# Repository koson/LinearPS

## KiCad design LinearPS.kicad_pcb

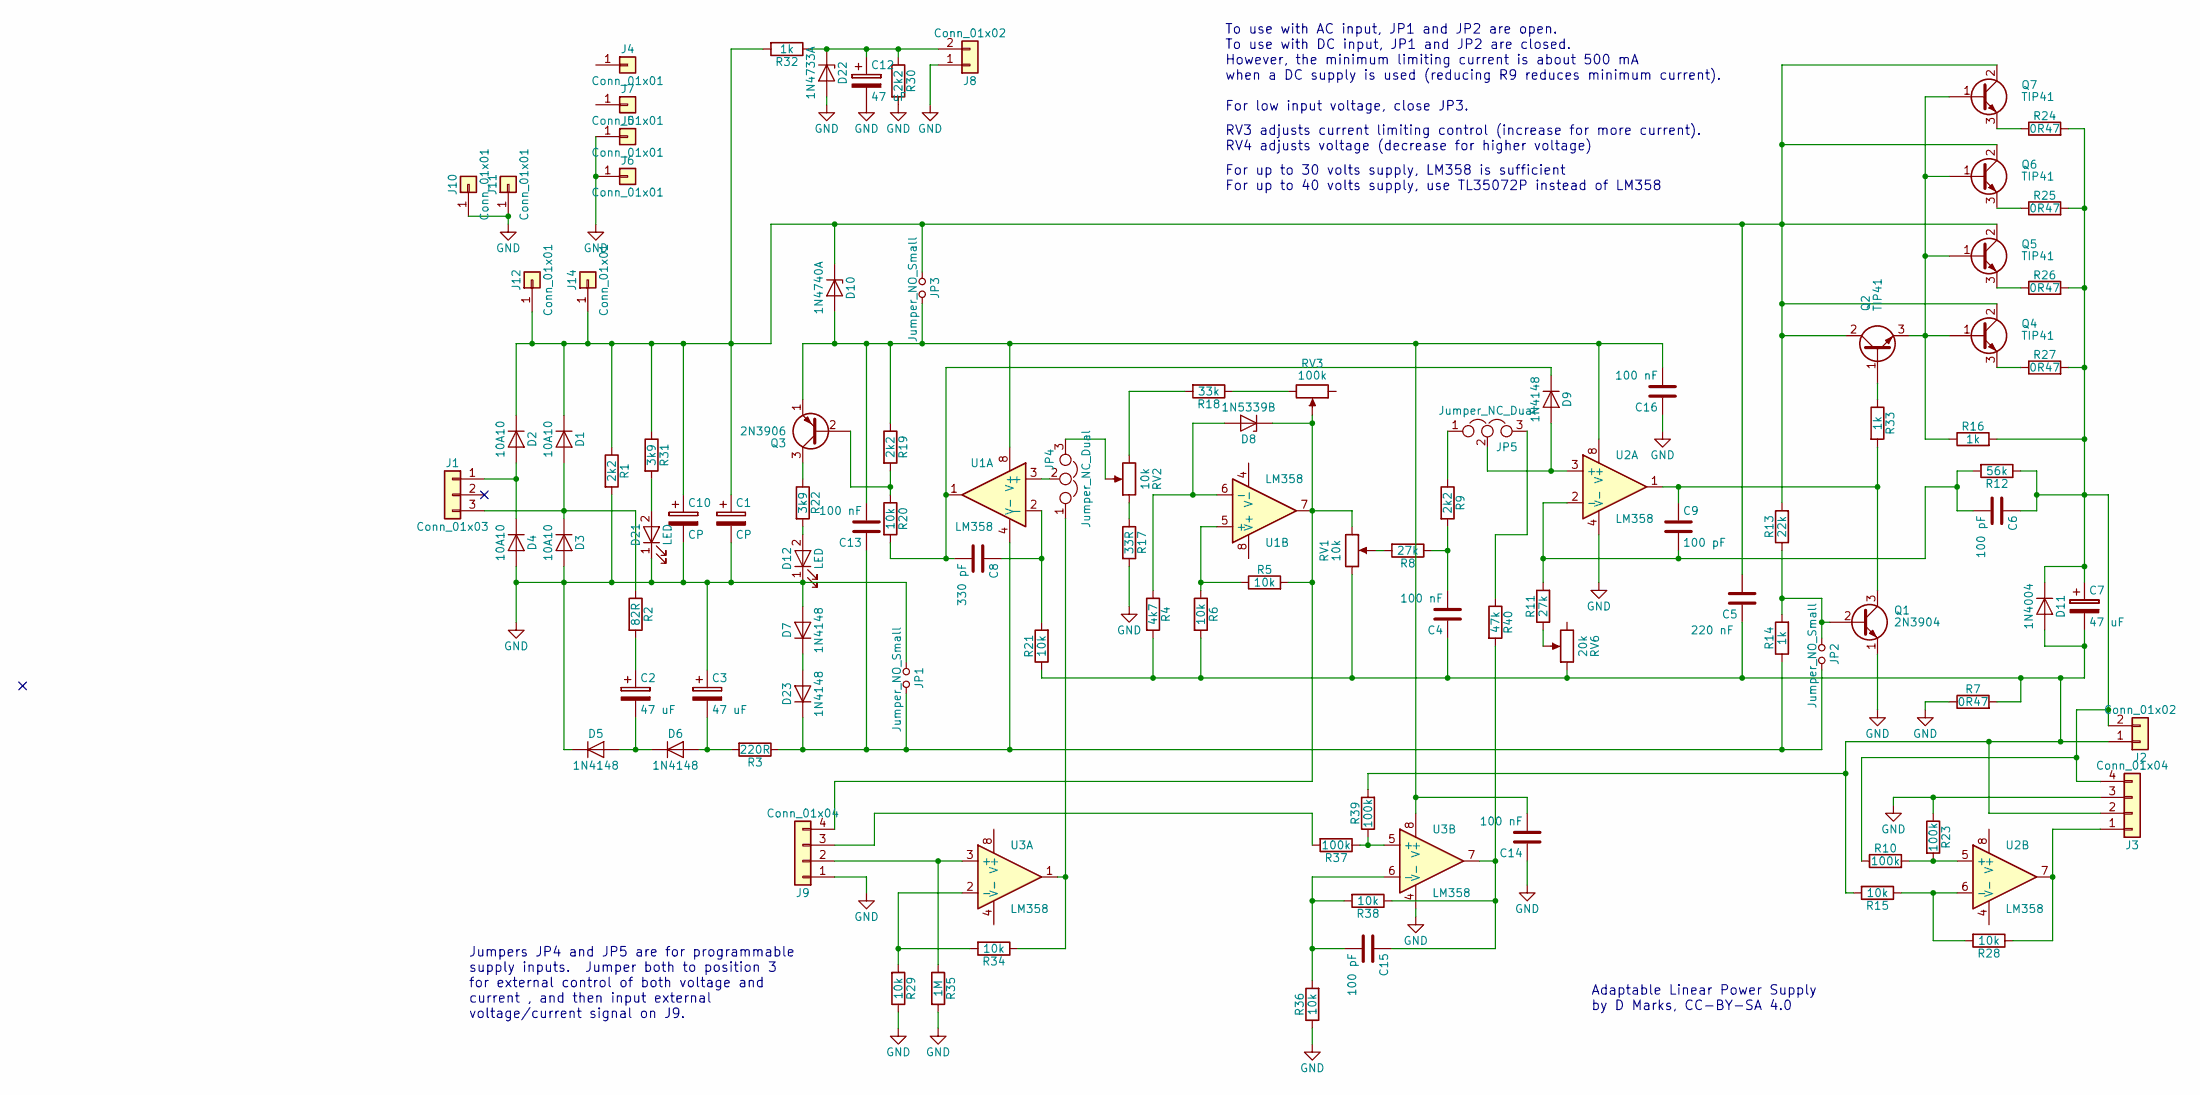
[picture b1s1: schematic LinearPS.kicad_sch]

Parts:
C1, C10: CP; CP_Radial_D18.0mm_P7.50mm
C2, C3, C7, C12: 47 uF; CP_Radial_D8.0mm_P5.00mm
C4, C13, C14, C16: 100 nF; C_Disc_D5.0mm_W2.5mm_P5.00mm
C5: 220 nF; C_Disc_D5.0mm_W2.5mm_P5.00mm
C6, C9, C15: 100 pF; C_Disc_D5.0mm_W2.5mm_P5.00mm
C8: 330 pF; C_Disc_D5.0mm_W2.5mm_P5.00mm
D1, D2, D3, D4: 10A10; D_P600_R-6_P12.70mm_Horizontal
D5, D6, D7, D9, D23: 1N4148; D_DO-35_SOD27_P7.62mm_Horizontal
D8: 1N5339B; D_DO-41_SOD81_P7.62mm_Horizontal
D10: 1N4740A; D_DO-41_SOD81_P7.62mm_Horizontal
D11: 1N4004; D_DO-41_SOD81_P7.62mm_Horizontal
D12, D21: LED; LED_D3.0mm
D22: 1N4733A; D_DO-41_SOD81_P7.62mm_Horizontal
J1: Conn_01x03; TerminalBlock_bornier-3_P5.08mm
J2: Conn_01x02; TerminalBlock_bornier-2_P5.08mm
J3, J9: Conn_01x04; Molex_KK-6410-04_04x2.54mm_Straight
J4, J5, J6, J7, J10, J11, J12, J14: Conn_01x01; 1pin
J8: Conn_01x02; Molex_KK-6410-02_02x2.54mm_Straight
JP1, JP2, JP3: Jumper_NO_Small; Pin_Header_Straight_1x02_Pitch2.54mm
JP4, JP5: Jumper_NC_Dual; Pin_Header_Straight_1x03_Pitch2.54mm
Q1: 2N3904; TO-92_Molded_Narrow
Q2: TIP41; TO-220-3_Vertical_WithPads
Q3: 2N3906; TO-92_Molded_Narrow
Q4, Q5, Q6, Q7: TIP41; TO-220-3_Vertical_WithBigPads
R1, R9, R19, R30: 2k2; R_Axial_DIN0207_L6.3mm_D2.5mm_P7.62mm_Horizontal
R2: 82R; R_Axial_DIN0411_L9.9mm_D3.6mm_P12.70mm_Horizontal
R3: 220R; R_Axial_DIN0411_L9.9mm_D3.6mm_P12.70mm_Horizontal
R4: 4k7; R_Axial_DIN0207_L6.3mm_D2.5mm_P7.62mm_Horizontal
R5, R6, R15, R20, R21, R28, R29, R34, R36, R38: 10k; R_Axial_DIN0207_L6.3mm_D2.5mm_P7.62mm_Horizontal
R7, R24, R25, R26, R27: 0R47; R_Axial_Power_L25.0mm_W6.4mm_P27.94mm
R8, R11: 27k; R_Axial_DIN0207_L6.3mm_D2.5mm_P7.62mm_Horizontal
R10, R23, R37, R39: 100k; R_Axial_DIN0207_L6.3mm_D2.5mm_P7.62mm_Horizontal
R12: 56k; R_Axial_DIN0207_L6.3mm_D2.5mm_P7.62mm_Horizontal
R13: 22k; R_Axial_DIN0207_L6.3mm_D2.5mm_P7.62mm_Horizontal
R14: 1k; R_Axial_DIN0207_L6.3mm_D2.5mm_P7.62mm_Horizontal
R16, R32, R33: 1k; R_Axial_DIN0411_L9.9mm_D3.6mm_P12.70mm_Horizontal
R17: 33R; R_Axial_DIN0207_L6.3mm_D2.5mm_P7.62mm_Horizontal
R18: 33k; R_Axial_DIN0207_L6.3mm_D2.5mm_P7.62mm_Horizontal
R22, R31: 3k9; R_Axial_DIN0207_L6.3mm_D2.5mm_P7.62mm_Horizontal
R35: 1M; R_Axial_DIN0207_L6.3mm_D2.5mm_P7.62mm_Horizontal
R40: 47k; R_Axial_DIN0207_L6.3mm_D2.5mm_P7.62mm_Horizontal
RV1, RV2: 10k; Potentiometer_WirePads
RV3: 100k; Potentiometer_Trimmer_Bourns_3296W
RV6: 20k; Potentiometer_Trimmer_Bourns_3296W
U1, U2, U3: LM358; DIP-8_W7.62mm_Socket

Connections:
GND: C1.2, C3.1, C10.2, C12.2, C14.1, C16.1, D3.2 (A), D4.2 (A), D5.1 (K), D7.2 (A), D12.1 (K), D21.1 (K), D22.2 (A), J3.3, J5.1, J6.1, J8.1, J9.1, J10.1, J11.1, JP1.1, Q1.1 (E), R1.2, R7.1, R17.2, R23.1, R29.1, R30.2, R35.2, R36.1, U2.4 (V-), U3.4 (V-)
unnamed: C1.1, C5.2, C10.1, D1.1 (K), D2.1 (K), D10.1 (K), J12.1, J14.1, JP3.1, Q2.2 (C), Q4.2 (C), Q5.2 (C), Q6.2 (C), Q7.2 (C), R1.1, R13.2, R31.1, R32.2
unnamed: C2.1, R2.2
unnamed: C2.2, D5.2 (A), D6.1 (K)
unnamed: C3.2, D6.2 (A), R3.2
unnamed: C4.1, C5.1, C7.2, D11.2 (A), J2.1, J3.2, R4.2, R6.2, R7.2, R15.2, R21.1, R39.2, RV1.3, RV6.1
unnamed: C4.2, R8.1, R9.2
unnamed: C6.1, C7.1, D11.1 (K), J2.2, J3.4, R10.1, R12.1, R16.2, R24.2, R25.2, R26.2, R27.2
unnamed: C6.2, C9.2, R11.2, R12.2, U2.2 (-)
unnamed: C8.1, R21.2, U1.2 (-)
unnamed: C8.2, D9.1 (K), R20.2, U1.1
unnamed: C9.1, Q1.3 (C), R33.2, U2.1
unnamed: C12.1, D22.1 (K), J8.2, R30.1, R32.1
unnamed: C13.1, D23.1 (K), JP1.2, JP2.2, R3.1, R14.1, U1.4 (V-)
unnamed: C13.2, C14.2, C16.2, D10.2 (A), JP3.2, Q3.1 (E), R19.1, U1.8 (V+), U2.8 (V+), U3.8 (V+)
unnamed: C15.1, R38.1, R40.2, U3.7
unnamed: C15.2, R36.2, R38.2, U3.6 (-)
unnamed: D1.2 (A), D3.1 (K), J1.3, R2.1
unnamed: D2.2 (A), D4.1 (K), J1.1
unnamed: D8.1 (K), J9.4, R5.2, RV1.1, RV3.2, U1.7
unnamed: D8.2 (A), R4.1, U1.6 (-)
unnamed: D9.2 (A), JP5.2, U2.3 (+)
unnamed: D12.2 (A), R22.2
unnamed: D21.2 (A), R31.2
unnamed: D7.1 (K), D23.2 (A)
unnamed: J3.1, R28.1, U2.7
unnamed: J9.2, R35.1, U3.3 (+)
unnamed: J9.3, R37.2
unnamed: JP2.1, Q1.2 (B), R13.1, R14.2
unnamed: JP4.1, R34.1, U3.1
unnamed: JP4.2, U1.3 (+)
unnamed: JP4.3, RV2.2
unnamed: JP5.1, R9.1
unnamed: JP5.3, R40.1
unnamed: Q2.1 (B), R33.1
unnamed: Q2.3 (E), Q4.1 (B), Q5.1 (B), Q6.1 (B), Q7.1 (B), R16.1
unnamed: Q3.2 (B), R19.2, R20.1
unnamed: Q3.3 (C), R22.1
unnamed: Q4.3 (E), R27.1
unnamed: Q5.3 (E), R26.1
unnamed: Q6.3 (E), R25.1
unnamed: Q7.3 (E), R24.1
unnamed: R5.1, R6.1, U1.5 (+)
unnamed: R8.2, RV1.2
unnamed: R10.2, R23.2, U2.5 (+)
unnamed: R11.1, RV6.2
unnamed: R15.1, R28.2, U2.6 (-)
unnamed: R17.1, RV2.1
unnamed: R18.1, RV3.3
unnamed: R18.2, RV2.3
unnamed: R29.2, R34.2, U3.2 (-)
unnamed: R37.1, R39.1, U3.5 (+)

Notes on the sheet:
Jumpers JP4 and JP5 are for programmable supply inputs. Jumper both to position 3 for external control of both voltage and current , and then input external voltage/current signal on J9.
To use with AC input, JP1 and JP2 are open. To use with DC input, JP1 and JP2 are closed. However, the minimum limiting current is about 500 mA when a DC supply is used (reducing R9 reduces minimum current). For low input voltage, close JP3.
RV3 adjusts current limiting control (increase for more current). RV4 adjusts voltage (decrease for higher voltage)
For up to 30 volts supply, LM358 is sufficient For up to 40 volts supply, use TL35072P instead of LM358
Adaptable Linear Power Supply by D Marks, CC-BY-SA 4.0

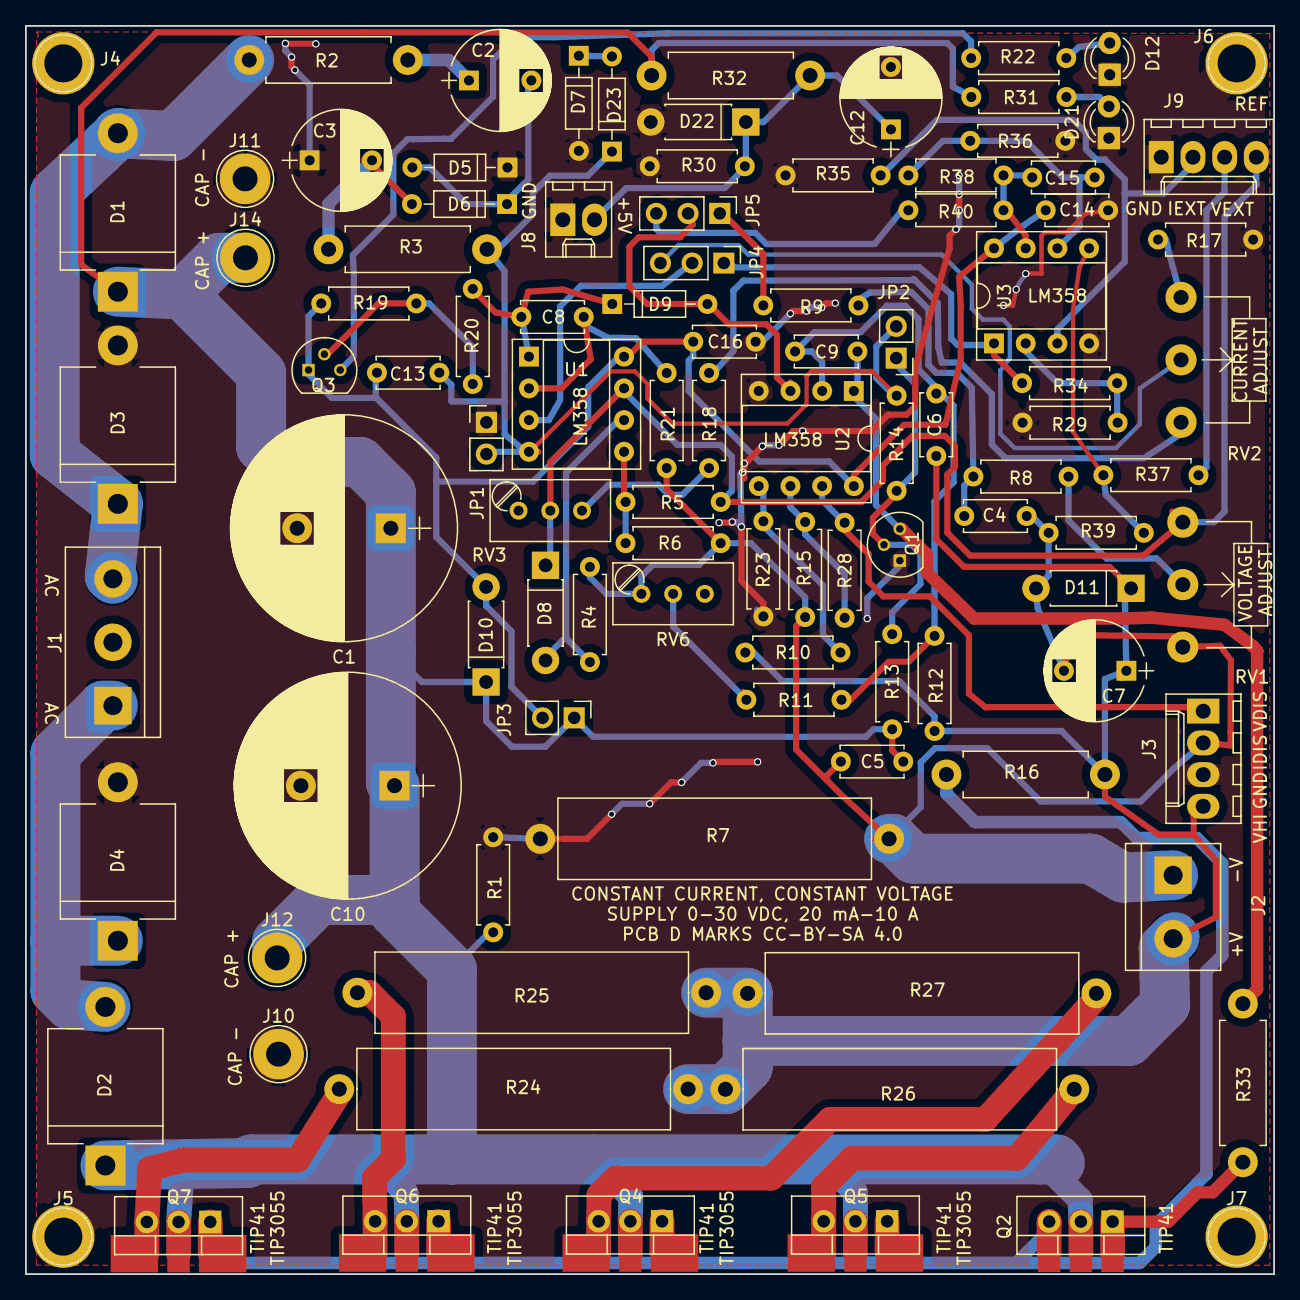
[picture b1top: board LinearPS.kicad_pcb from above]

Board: 2 copper layers, 100.0 x 100.0 mm, 102 parts (0 on the bottom side), 52 nets.

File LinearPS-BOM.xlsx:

Source: | F:\OneDrive\__PCB Works\LinearPS\LinearPS.kicad_sch
Date: | 44359.901342592595
Tool: | Eeschema (5.99.0-10447-gf083f043cb)
Generator: | C:\Program Files\KiCad\5.99\bin\scripting\plugins/bom_csv_grouped_by_value.py
Component Count: | 102
Item | Qty | Reference(s) | Value | LibPart | Footprint | Datasheet | Description | Part_Number
1 | 2 | C1, C10 | CP | LinearPS-rescue:CP | Capacitors_THT:CP_Radial_D18.0mm_P7.50mm | http://www.es.co.th/detail.asp?Prod=056603488 | E-Cap KM Series 4700uF/50Vdc -40 C to +105 C, 20% ,2000hrs. Miniature Sized | EKM478M1HL40RRSAP
2 | 4 | C2, C3, C7, C12 | 47 uF | LinearPS-rescue:CP | Capacitors_THT:CP_Radial_D8.0mm_P5.00mm | http://www.es.co.th/detail.asp?Prod=056601120 | E-Cap GS Series 4.7uF/400Volt | EGS475M2GF12RRSAP
3 | 4 | C4, C13, C14, C16 | 100 nF | LinearPS-rescue:C | Capacitors_THT:C_Disc_D5.0mm_W2.5mm_P5.00mm | http://www.es.co.th/detail.asp?Prod=015800183 | Ceramic Disc Cap 0.1uF/50V, -20/+80% Dia 7.5mm | S104ZYFE072L
4 | 1 | C5 | 220 nF | LinearPS-rescue:C | Capacitors_THT:C_Disc_D5.0mm_W2.5mm_P5.00mm | http://www.es.co.th/detail.asp?Prod=015802865 | Ceramic Disc Cap 0.22uF/50Vdc, -20/+80%,Y5V | S224ZYFE082LF
5 | 3 | C6, C9, C15 | 100 pF | LinearPS-rescue:C | Capacitors_THT:C_Disc_D5.0mm_W2.5mm_P5.00mm | http://www.es.co.th/detail.asp?Prod=015800245 | Ceramic Disc Cap 100pF/50Vdc, 10% | T101KCHE062L
6 | 1 | C8 | 330 pF | LinearPS-rescue:C | Capacitors_THT:C_Disc_D5.0mm_W2.5mm_P5.00mm | http://www.es.co.th/detail.asp?Prod=015802125 | Ceramic Disc Cap 330pF/50Vdc, 10% | H331KYAE052A-T
7 | 4 | D1, D2, D3, D4 | 10A10 | LinearPS-rescue:D | Diodes_THT:D_P600_R-6_P12.70mm_Horizontal
8 | 5 | D5, D6, D7, D9, D23 | 1N4148 | LinearPS-rescue:D | Diodes_THT:D_DO-35_SOD27_P7.62mm_Horizontal | http://www.es.co.th/detail.asp?Prod=029901371 | Fast Switching Diodes 100V/200mA trr 4ns | PH1N4148TB
9 | 1 | D8 | 1N5339B | LinearPS-rescue:D_Zener | Diodes_THT:D_DO-41_SOD81_P7.62mm_Horizontal | http://www.es.co.th/detail.asp?Prod=013500933 | ZENER DIODE 5.6V/1.3W, Iz=45mA | 1N4734A-TAP
10 | 1 | D10 | 1N4740A | LinearPS-rescue:D_Zener | Diodes_THT:D_DO-41_SOD81_P7.62mm_Horizontal | http://www.es.co.th/detail.asp?Prod=029900847 | Zener Diodes 1W/10V , Iz= 25mA Hermetically Sealed Glass Zener Voltage Regulator | 1N4740ATA-TC/ON
11 | 1 | D11 | 1N4004 | LinearPS-rescue:D | Diodes_THT:D_DO-41_SOD81_P7.62mm_Horizontal | http://www.es.co.th/detail.asp?Prod=030800029 | Silicon Rectifiers Diode 400V/1A | 1N4004-JJ
12 | 2 | D12, D21 | LED | LinearPS-rescue:LED | LEDs:LED_D3.0mm | http://www.es.co.th/detail.asp?Prod=001000491 | LED Round 3mm,4mcd,Red Color Red Diffused Lens | TOL-30BHRADAA
13 | 1 | D22 | 1N4733A | LinearPS-rescue:D_Zener | Diodes_THT:D_DO-41_SOD81_P7.62mm_Horizontal | http://www.es.co.th/detail.asp?prod=029900727 | Zener Diodes 1W/5.1V, Iz = 49mA Hermetically Sealed Glass Zener Voltage Regulat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 | 1N4733ATA-TC/ON
14 | 1 | J1 | Conn_01x03 | LinearPS-rescue:Conn_01x03 | Connectors_Terminal_Blocks:TerminalBlock_bornier-3_P5.08mm
15 | 1 | J2 | Conn_01x02 | LinearPS-rescue:Conn_01x02 | Connectors_Terminal_Blocks:TerminalBlock_bornier-2_P5.08mm
16 | 2 | J3, J9 | Conn_01x04 | LinearPS-rescue:Conn_01x04 | Connectors_Molex:Molex_KK-6410-04_04x2.54mm_Straight
17 | 8 | J4, J5, J6, J7, J10, J11, J12, J14 | Conn_01x01 | LinearPS-rescue:Conn_01x01 | Connectors:1pin
18 | 1 | J8 | Conn_01x02 | LinearPS-rescue:Conn_01x02 | Connectors_Molex:Molex_KK-6410-02_02x2.54mm_Straight
19 | 3 | JP1, JP2, JP3 | Jumper_NO_Small | LinearPS-rescue:Jumper_NO_Small | Pin_Headers:Pin_Header_Straight_1x02_Pitch2.54mm
20 | 2 | JP4, JP5 | Jumper_NC_Dual | LinearPS-rescue:Jumper_NC_Dual | Pin_Headers:Pin_Header_Straight_1x03_Pitch2.54mm
21 | 1 | Q1 | 2N3904 | LinearPS-rescue:2N3904 | TO_SOT_Packages_THT:TO-92_Molded_Narrow | http://www.es.co.th/detail.asp?prod=012302944 | Transistor NPN 40V/0.2A,for General Purpose Amplifier and Switch, Useful Dynami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 | 2N3904TA
22 | 1 | Q2 | TIP41 | LinearPS-rescue:TIP41 | linearps:TO-220-3_Vertical_WithPads | http://www.es.co.th/detail.asp?prod=008304245 | Silicon Power Transistors NPN 100V/6A Medium Power Linear and Switching Applica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 | TIP41C
23 | 1 | Q3 | 2N3906 | LinearPS-rescue:2N3906 | TO_SOT_Packages_THT:TO-92_Molded_Narrow | http://www.es.co.th/detail.asp?Prod=012302600 | Transistor PNP 40V/0.2A for General Purpose Amplifier and Switching Application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 | 2N3906TA
24 | 4 | Q4, Q5, Q6, Q7 | TIP41 | LinearPS-rescue:TIP41 | linearps:TO-220-3_Vertical_WithBigPads | http://www.es.co.th/detail.asp?prod=008304245 | Silicon Power Transistors NPN 100V/6A Medium Power Linear and Switching Applica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 | TIP41C
25 | 4 | R1, R9, R19, R30 | 2k2 | LinearPS-rescue:R | Resistors_THT:R_Axial_DIN0207_L6.3mm_D2.5mm_P7.62mm_Horizontal |  |  | R 2k2 1/4W 5%
26 | 1 | R2 | 82R | LinearPS-rescue:R | Resistors_THT:R_Axial_DIN0411_L9.9mm_D3.6mm_P12.70mm_Horizontal |  |  | R 82E 1W 5%
27 | 1 | R3 | 220R | LinearPS-rescue:R | Resistors_THT:R_Axial_DIN0411_L9.9mm_D3.6mm_P12.70mm_Horizontal |  |  | R 220E 1W 5%
28 | 1 | R4 | 4k7 | LinearPS-rescue:R | Resistors_THT:R_Axial_DIN0207_L6.3mm_D2.5mm_P7.62mm_Horizontal |  |  | R 4k7 1/4W 5%
29 | 10 | R5, R6, R15, R20, R21, R28, R29, R34, R36, R38 | 10k | LinearPS-rescue:R | Resistors_THT:R_Axial_DIN0207_L6.3mm_D2.5mm_P7.62mm_Horizontal |  |  | R 10k 1/4W 5%
30 | 5 | R7, R24, R25, R26, R27 | 0R47 | LinearPS-rescue:R | Resistors_THT:R_Axial_Power_L25.0mm_W6.4mm_P27.94mm |  |  | R 0R47 5W 5%
31 | 2 | R8, R11 | 27k | LinearPS-rescue:R | Resistors_THT:R_Axial_DIN0207_L6.3mm_D2.5mm_P7.62mm_Horizontal |  |  | R 27k 1/4W 5%
32 | 4 | R10, R23, R37, R39 | 100k | LinearPS-rescue:R | Resistors_THT:R_Axial_DIN0207_L6.3mm_D2.5mm_P7.62mm_Horizontal |  |  | R 100k 1/4W 5%
33 | 1 | R12 | 56k | LinearPS-rescue:R | Resistors_THT:R_Axial_DIN0207_L6.3mm_D2.5mm_P7.62mm_Horizontal |  |  | R 56k 1/4W 5%
34 | 1 | R13 | 22k | LinearPS-rescue:R | Resistors_THT:R_Axial_DIN0207_L6.3mm_D2.5mm_P7.62mm_Horizontal |  |  | R 22k 1/4W 5%
35 | 1 | R14 | 1k | LinearPS-rescue:R | Resistors_THT:R_Axial_DIN0207_L6.3mm_D2.5mm_P7.62mm_Horizontal |  |  | R 1k 1/4W 5%
36 | 3 | R16, R32, R33 | 1k | LinearPS-rescue:R | Resistors_THT:R_Axial_DIN0411_L9.9mm_D3.6mm_P12.70mm_Horizontal |  |  | R 1k 1W 5%
37 | 1 | R17 | 33R | LinearPS-rescue:R | Resistors_THT:R_Axial_DIN0207_L6.3mm_D2.5mm_P7.62mm_Horizontal |  |  | R 33R 1/4W 5%
38 | 1 | R18 | 33k | LinearPS-rescue:R | Resistors_THT:R_Axial_DIN0207_L6.3mm_D2.5mm_P7.62mm_Horizontal |  |  | R 33k 1/4W 5%
39 | 2 | R22, R31 | 3k9 | LinearPS-rescue:R | Resistors_THT:R_Axial_DIN0207_L6.3mm_D2.5mm_P7.62mm_Horizontal |  |  | R 3k9 1/4W 5%
40 | 1 | R35 | 1M | LinearPS-rescue:R | Resistors_THT:R_Axial_DIN0207_L6.3mm_D2.5mm_P7.62mm_Horizontal |  |  | R 1M 1/4W 5%
41 | 1 | R40 | 47k | LinearPS-rescue:R | Resistors_THT:R_Axial_DIN0207_L6.3mm_D2.5mm_P7.62mm_Horizontal |  |  | R 47k 1/4W 5%
42 | 2 | RV1, RV2 | 10k | LinearPS-rescue:POT | Potentiometers:Potentiometer_WirePads |  |  | Volume 10kB
43 | 1 | RV3 | 100k | LinearPS-rescue:POT | Potentiometers:Potentiometer_Trimmer_Bourns_3296W | http://www.es.co.th/detail.asp?prod=014102719 | Trimpot 25 Turns,100k, 10%, 0.5 w. | 3296W-1-104LF
44 | 1 | RV6 | 20k | LinearPS-rescue:POT | Potentiometers:Potentiometer_Trimmer_Bourns_3296W | http://www.es.co.th/detail.asp?prod=014102631 | Trimpot 25 Turns,20k,10%, 0.5 w. | 3296W-1-203LF
45 | 3 | U1, U2, U3 | LM358 | LinearPS-rescue:LM358 | Housings_DIP:DIP-8_W7.62mm_Socket | http://www.es.co.th/detail.asp?Prod=008607238 | Dual Op-Amp,Unity Gain Bandwidth 700kHz Slew Rate 0.3V/us,Input Offset Voltage 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 | LM358P

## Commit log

2021-05-29 upgrade to Kicad_599
2021-05-29 Create fp-info-cache
2021-06-12 Update fp-info-cache

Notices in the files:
LinearPS.kicad_pcb:
PCB D MARKS CC-BY-SA 4.0
